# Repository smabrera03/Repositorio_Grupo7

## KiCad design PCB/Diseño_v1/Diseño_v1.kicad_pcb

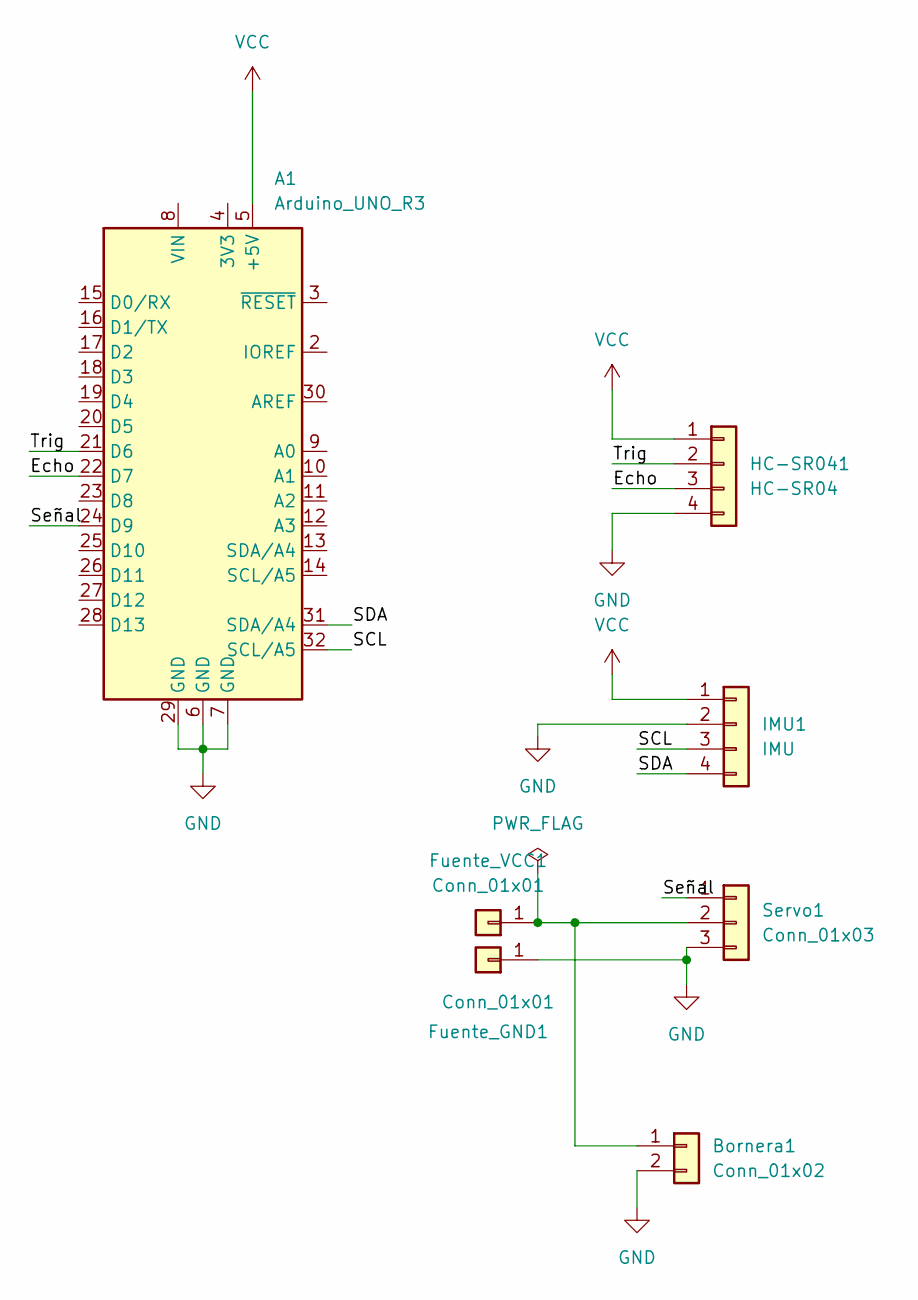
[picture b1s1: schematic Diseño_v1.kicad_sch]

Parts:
A1: Arduino_UNO_R3
Bornera1: Conn_01x02; TerminalBlock_MaiXu_MX126-5.0-02P_1x02_P5.00mm
Fuente_GND1: Conn_01x01; PinHeader_1x01_P2.54mm_Vertical
Fuente_VCC1: Conn_01x01; PinHeader_1x01_P2.54mm_Vertical
HC-SR041: HC-SR04; PinHeader_1x04_P2.54mm_Vertical
IMU1: IMU; PinHeader_1x04_P2.54mm_Vertical
Servo1: Conn_01x03; PinHeader_1x03_P2.54mm_Vertical

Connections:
/Echo: A1.22 (D7), HC-SR041.3
/SCL: A1.32 (SCL/A5), IMU1.3
/SDA: A1.31 (SDA/A4), IMU1.4
/Señal: A1.24 (D9), Servo1.1
/Trig: A1.21 (D6), HC-SR041.2
GND: A1.6 (GND), A1.7 (GND), A1.29 (GND), Bornera1.2, Fuente_GND1.1 (Pin_1_1), HC-SR041.4, IMU1.2, Servo1.3
unnamed: Bornera1.1, Fuente_VCC1.1 (Pin_1_1), Servo1.2
VCC: A1.5 (+5V), HC-SR041.1, IMU1.1

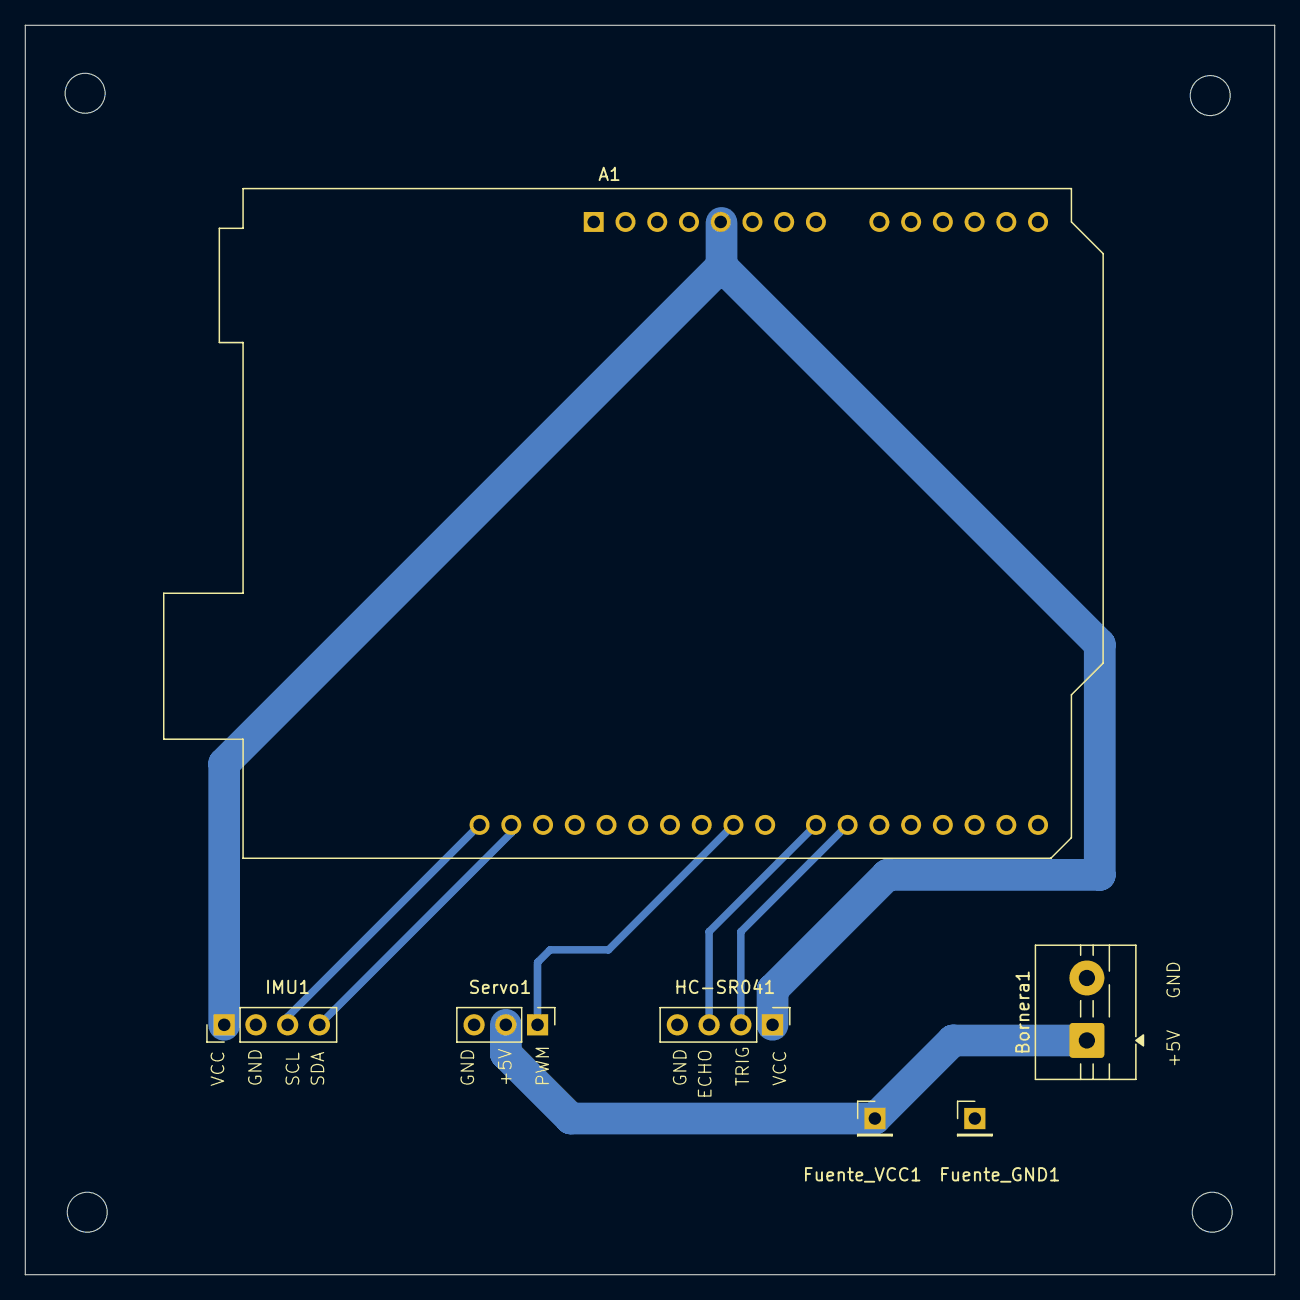
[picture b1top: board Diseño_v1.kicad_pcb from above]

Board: 2 copper layers, 100.0 x 100.0 mm, 7 parts (0 on the bottom side), 8 nets.

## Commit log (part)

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2026-03-28 Primer commit
2026-04-01 práctica 2
2026-04-07 continua la práctica 2
2026-04-11 Arrancando tp1
2026-04-11 seguimos
2026-04-11 Mediciones TP
2026-04-11 nombre mal escrito
2026-04-12 Tiempo de envío de floats y datasheet del servo
2026-04-12 Nuevos códigos para medir. Servirán?
2026-04-12 Adjunto archivos correspondientes al TP1
2026-04-12 mi primir commit
2026-04-12 ignorar .DS_Store
2026-04-12 Limpieza total: eliminar .DS_Store del repo
2026-04-12 Prueba Git LGV
2026-04-13 Cambié un poco el código para medir tiempo
2026-04-13 Agrefo hojas de datos
2026-04-14 Agrego informe
2026-04-14 Agrego Informe pdf
2026-04-14 No sé qué cambié
2026-04-14 Corrección informe
2026-04-14 Práctica 3
2026-04-15 practica 3
2026-04-15 Elimino .zip
2026-04-22 Práctica 4
2026-04-26 cuentas y pcb
2026-04-26 corregí el gitignore
2026-04-27 Modifiqué el PCB
2026-04-28 Volví a cambiar el PCB
2026-04-28 Practica 6
2026-04-29 Práctica 6. Salió todo mal lcdll
2026-05-01 avanzamos con el tp2
2026-05-06 Me cago en el balancín de mierda y en la puta que lo parió
2026-05-11 Avances tp2
2026-05-12 planta identificada
2026-05-12 notas de cuadrados mínimos restringidos
2026-05-12 corrección resultados importantes.txt
2026-05-12 me di cuenta de que está todo mal
2026-05-12 Seguí participando
2026-05-13 corrección
2026-05-13 probando más cosas. sin exito
2026-05-13 borré algo
2026-05-18 Modif.
2026-05-18 Agrego comentarios al .ino
2026-05-19 Agrego imagen planta
2026-05-19 Controladores PD y PI
2026-05-19 Agrego teóricas
2026-05-20 práctica 7 y tp2
2026-05-23 agregué una imagen
2026-05-23 Imágenes informe
2026-05-23 Cambios en el PD
2026-05-24 más imágenes tp2
2026-05-24 Nuevas fotos
2026-05-24 otra imagen
2026-05-26 Practica 5
2026-05-26 "Con la terminal hacés mucho más rápido"
2026-06-03 práctica 9
2026-06-03 correciones practica 8
2026-06-09 consigna
2026-06-10 Observador TP3
2026-06-17 Avances tp3
2026-06-19 TP3 Fran y Valen
2026-06-20 UNA BANDA DE IMAGENES
2026-06-21 correción observador
2026-06-23 intenté corregir el observador sin mucho éxito
2026-06-24 fin tp3?
2026-06-30 me cago en esta planta de mierda
2026-06-30 prueba final
2026-06-30 ultimo commit (espero)
